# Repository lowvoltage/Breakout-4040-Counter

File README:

Breakout PCB for the CMOS 4040 Counter IC in DIP package

KiCAD schematic and PCB layout by Dimitar Kovachev

Released under the Creative Commons Attribution Share-Alike 3.0 license
http://creativecommons.org/licenses/by-sa/3.0/

Used libraries and 3D models:
http://smisioto.no-ip.org/elettronica/kicad/kicad-en.htm

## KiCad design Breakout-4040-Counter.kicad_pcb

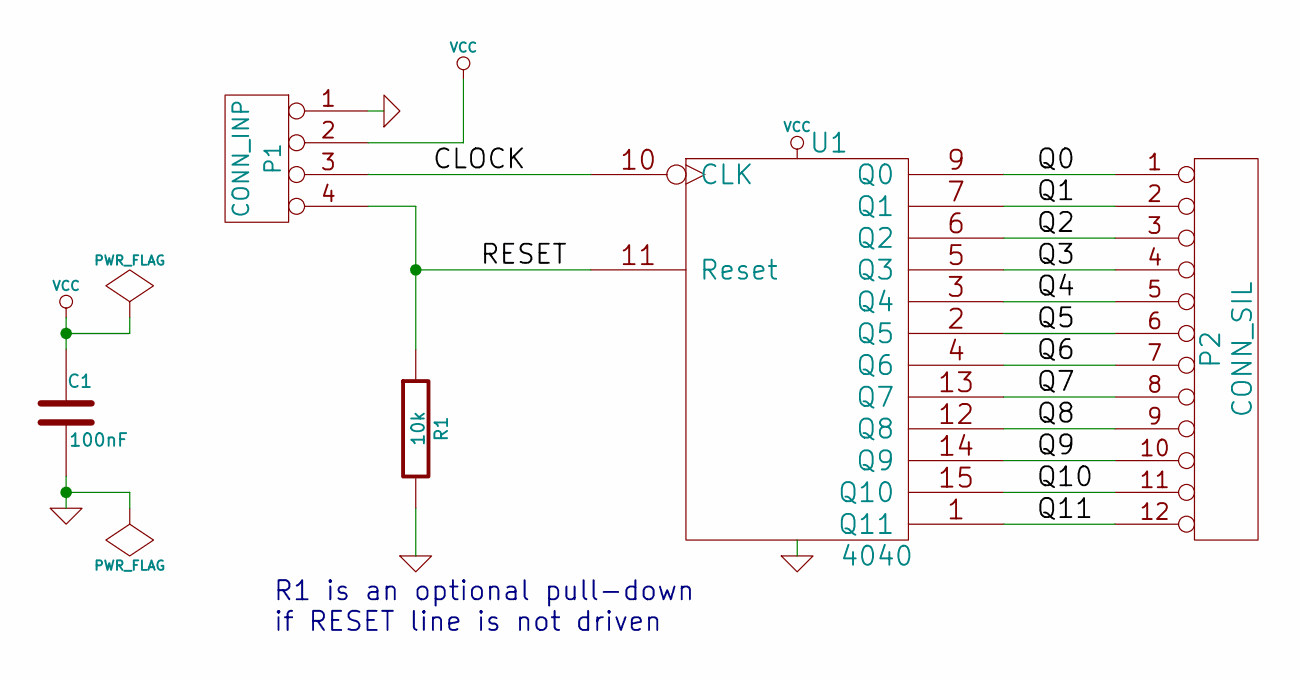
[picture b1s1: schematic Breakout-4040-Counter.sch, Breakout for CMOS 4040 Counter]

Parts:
C1: 100nF
P1: CONN_INP
P2: CONN_SIL
R1: 10k
U1: 4040

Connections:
/CLOCK: P1.3, U1.10 (CLK)
/Q0: P2.1, U1.9 (Q0)
/Q1: P2.2, U1.7 (Q1)
/Q2: P2.3, U1.6 (Q2)
/Q3: P2.4, U1.5 (Q3)
/Q4: P2.5, U1.3 (Q4)
/Q5: P2.6, U1.2 (Q5)
/Q6: P2.7, U1.4 (Q6)
/Q7: P2.8, U1.13 (Q7)
/Q8: P2.9, U1.12 (Q8)
/Q9: P2.10, U1.14 (Q9)
/Q10: P2.11, U1.15 (Q10)
/Q11: P2.12, U1.1 (Q11)
/RESET: P1.4, R1.1, U1.11 (Reset)
GND: C1.2, P1.1, R1.2, U1.8 (VSS)
VCC: C1.1, P1.2, U1.16 (VDD)

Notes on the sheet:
R1 is an optional pull-down if RESET line is not driven

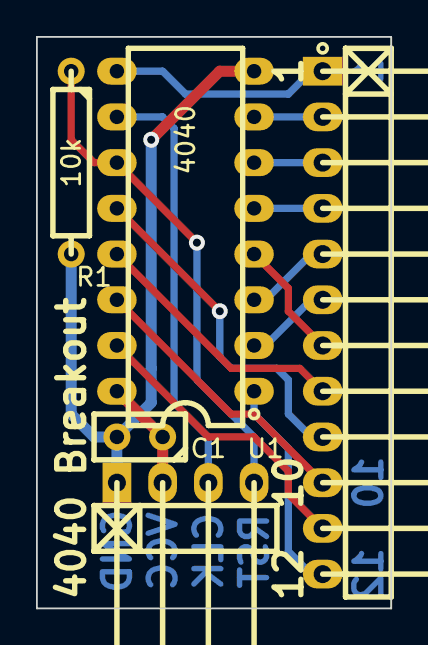
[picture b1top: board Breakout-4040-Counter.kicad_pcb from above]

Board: 2 copper layers, 19.7 x 31.8 mm, 5 parts (0 on the bottom side), 16 nets.
